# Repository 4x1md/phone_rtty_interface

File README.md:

# RTTY/AFSK Interface for Android Phone or Tablet

## Overview

This interface board was designed for experimenting with RTTY, SSTV and other digital modes with my Yaesu FT-817ND transceiver using [DroidRTTY](https://play.google.com/store/apps/details?id=com.wolphi.droidrtty&hl=en) and [DroidSSTV](https://play.google.com/store/apps/details?id=com.wolphi.sstv&hl=en) applications on an Android phone.

## Reference circuits

The idea of this circuit is not new. Many of its variants were published in the internet and the difference between them is relatively small. Usually different versions use different transistors and diodes and some resistors and capacitors values vary but the circuit remains the same.

One of my sources was the article [An AFSK Interface for Android Smartphones](https://github.com/4x1md/phone_rtty_interface/blob/master/docs/An_AFSK_Interface_for_Android_Smartphones.pdf) by Wolfgang Philips, W8DA, and Martin Huyett, K0BXB, which was published in the May 2012 issue of QST.

More circuits are available in [links section](#links) of this document.

## Revision A

The interface has two revisions. The difference between the two is relatively small. Circuit description and mechanics presented further down in this document are relevant for both revisions.

For the schematics and the photos of the first revision please refer to [revision_a.md](https://github.com/4x1md/phone_rtty_interface/blob/master/docs/revision_a.md)

If you got a blue PCB from me, you have the first revision board.

## Schematic

J1 connects the interface to a phone or tablet. It is a generic 4-pole 3.5mm jack. Its pinout is the same as that of Android phones. Using this jack makes connecting the phone or tablet easy requiring only a simple 3.5mm-to-3.5mm TRRS jack cable. No custom cables are required.

R1 and R2 prevent short-circuit of phone outputs. Their values are not critical and can be in the range of 10 to 51 Ohm. R1 connects the output of the right channel and R2 connects the left. One channel or both can be used. If only one channel is used, only the corresponding resistor should be assembled. In this configuration a wire jumper can be used instead of a resistor.

Transistor Q1 is a common emitter voltage amplifier stage. It is powered from the phone by the DC voltage which usually powers external microphone.

The bias resistors of this stage are R3, R4 and R5. These three resistors allow building two different amplifier types. All the three should not be assembled at the same time. Assembling R5 only creates a shunt feedback stage. In this case R3 and R4 are not required. If R3 and R4 are assembled the amplifier becomes voltage divider biased stage without AC feedback. In this case R5 is not required. These three resistor footprints leave some field for experimenting which is an essential part of the amateur radio.

Diodes D1 and D2 rectify the amplified signal and create DC bias for Q2 which pulls down the PTT line of the transceiver. Different versions of this circuit use different types of diodes. Some use silicon diodes, others use Shottkys. My assembled version worked well with 1N4148 silicon diodes. Replacing them with BAT46 Shottkys increased the rectifier output voltage. Germanium diodes like 1N34 or 1N60 should work as well in this circuit.

Transistor Q2 pulls the PTT line of the transceiver down. The PTT line of FT-817ND has pull-up resistors network with total resistance of 11 kOhm. It means that the current needed to pull the PTT voltage down to zero is 0.45 mA. It requires bias current of Q2 to be about 20 microamperes. In actual circuit the voltage on C6 will be about 0.8V which will be enough to bias Q2 into saturation.

Resistor R15 discharges C6 when the PTT line needs to be released. It is required if Q2 is a MOSFET. It was added in the second version of the interface.

The design features two connectors for connecting a transceiver. P1 is a 6-pin mini-DIN connector which is pin-compatible with DATA connector of Yaesu FT-817. The second connector, J2 is 4-pole 3.5mm jack. It is a generic connector which can also be used to connect transceivers. The 3.5mm TRRS jack does not have PTT line. Two connectors are put for redundancy. In actual circuit only one or both can be assembled depending on requirements.

Both connectors have 1200 bps and 9600 bps lines and switch SW1 is used to choose between the two data rates. If only one data rate is required, the corresponding switch pins can be shorted with a wire jumper without assembling the switch itself.

C7 and C8 are RF-blocking capacitors thus ceramic ones are preferred. Other components are not critical. Most of them can be pulled of old electronic equipment.

## Circuit analysis

If you like exploring oscilloscope output, doing some math and want more details about this circuit, please refer to [circuit_description.md](https://github.com/4x1md/phone_rtty_interface/blob/master/docs/circuit_description.md).

If you like simulating circuits, refer to [circuit_simulations.md](https://github.com/4x1md/phone_rtty_interface/blob/master/docs/circuit_simulations.md) for LTspice simulations.

## BOM variants

The second revision of the interface Q2 can be BJT or MOSFET.

### BJT version

### MOSFET version

The rectifier output voltage reaches approximately 2.2V when loaded with a high resistance. Therefore, a low threshold N-channel MOSFET is recommended for this circuit. For example, VN2410L has maximum Vth of 2.0V, which makes it a good choice. However, a general purpose MOSFET with a higher Vth might work too. In my circuit I used 2N7000 which has maximum threshold of 3.0V and it works well.

If Q2 is a MOSFET, R15 is require for discharging C6. Without R15, C6 will remain charged after the first transmit and the PTT line will never be released.

## Connectors pinout

The following diagram shows the pinout of the external connectors. The phone is connected using 3.5mm jack J1. The transceiver can be connected to the 6-pin Mini-DIN connector P1 or to the 3.5mm jack J2. Connectors P1 and J2 are electrically connected. The PTT line is connected to P1 only.

## Design

### Requirements and considerations

 - Enclosure box.
 - Small size.
 - Easy-to-get parts.
 - Adjusting potentiometers from front or rear panel.
 - No proprietary connectors.
 - Easy assembly.
 - Good repeatability by other hams.
 - Options for experiments.

### Mechanics

When I started the development, I decided to assemble the device in an enclosure box. The box had to be inexpensive and easily available from different electronic parts suppliers.

After some search I found a blue aluminium box 58x50x24mm. The box is relatively cheap and can be purchased from many sellers on eBay or AliExpress. The box fits a PCB of 50x50mm which is enough for this project and has front and rear panels which can be modified by drilling or cutting. In order to eliminate the drilling process, in revision B I created front and rear panels from PCBs.

### PCB development

The PCB was designed using KiCAD software as a simple two-layer board with through-hole mounted parts.

<!--  -->

<!--  -->

### Front and rear panels

Both front and rear panels were made from PCBs. Their fuction is mechanical only and no electronic parts are assembled on these PCBs.

## Photo gallery

### Factory-produced PCB

The PCBs were produced by PCBWay who did a great job. Solder mask of the first revision was made blue in order to match the color of the enclosure box. The second revision was produced with green solder mask.

<!--  -->

:warning: **Important Note!**
Minimum order at the factory was 10 boards from which I need only two or three. As of April 15, 2020, I have board sets (main PCB, front and rear panel), which I can give away. If you'd like to build this device for yourself, I can send you a board. Feel free to contact me.

### Populated PCB

The design uses through hole parts which make PCB assembly quite simple. Connectors, trimmer potentiometers and switch are new. All the other components were recovered from old electronic equipment.

### Assembled device

I haven't yet completed drilling the front and the rear panel of the box, so the device isn't yet fully assembled. The following photos show that the PCB perfectly fits in the chosen box.

The complete device with front and rear panel assembled:

### Field tests and using the device

Cuba to Israel. Nice DX!

## Known issues

The developers of [Wolphi-Link interface](http://www.wolphi.com/interface/) report the following issue:

```WolphiLink might not work properly if you transmit on VHF or UHF while having your antenna to close to your phone/tablet and WolphiLink. The PTT might get triggered by RF and would not release.```

I experienced the same behavior on VHF and UHF bands especially when trying to transmit in AM, FM or PKT modes. When the transmitting antenna is close to the board the transceiver remains in TX mode and the only way to release it is to turn it off. The issue usually disappears when the phone is disconnected even if its cable is still connected to the jack.

I suppose that the cables between the transceiver and the phone become a counterpoise of the transmitting antenna and the generated RF causes transceiver keying. I don't know if this issue exists with other transceivers.

Till now, I couldn't find any solution. On HF bands and when the transmitting antenna is far from the transceiver the device functions properly.

**Update:** After connecting a shielded cable between the transceiver and the interface, the problem is almost completely.

## Adjustments

A properly assembled device should require only RX and TX level adjustments using R10 and R11 trimmer potentiometers.

## Plans for future development

If I ever do another revision of this board, I'd like to make the following improvements:

1. [x] Adding an RF-blocking capacitor to the PTT line.
2. [x] Adding PTT line to J2 3.5mm jack.
3. [x] Adding a capacitor in parallel to R5 for limiting the bandwidth of the amplifier.
4. [x] Removing ground conductor from the component layer.
5. [x] Improving the thermal relief on the grounded pads. Today they are sometimes hard to solder.
6. [x] Increasing the space between R10 and R11 to fit larger trimmer resistors.
7. [ ] Adding a TX inhibit switch which will disable triggering the PTT line. It may be useful to prevent notifications or other non radio-related sounds to key the transceiver.

## Links
* Designing a Phone/Radio interface: [Part 1](https://waynemerry.wordpress.com/2012/08/16/designing-a-phoneradio-interface/), [Part 2](https://waynemerry.wordpress.com/2012/08/22/ft-817-phone-audio-interface-part-2/), [Part 3](https://waynemerry.wordpress.com/2012/11/02/ft-817-ft-897-phone-audio-interface-part-3/)
* http://www.darc-husum.de/android-interface.html
* https://www.dk9jc.de/blog/equipment/109-ft-817-smartphone-interface-for-pskdroid-and-aprsdroid
* [DroidSSTV manual](http://www.wolphi.com/ham-radio-apps/droidsstv-2/droidsstv-manual/)
* [Wolphi-Link interface](http://www.wolphi.com/interface/)
* http://161wt001.blogspot.com/2013/11/construction-interface-sstv-psk-rtty.html
* https://oe6fte.com/wolphilink-android-interface/
* https://g4fre.blogspot.com/2014/02/rtty-and-psk31-transceive-with-nexus-7.html
* http://wa8lmf.net/ham/tonekeyer.htm
* https://9m2pju.blogspot.com/2012/05/droidpsk-psk-on-your-android-phone.html
* Enclosure box: http://www.ebay.com/itm/171186884639

## Questions? Suggestions?
You are more than welcome to contact me with any questions, suggestions or propositions regarding this project. You can:

1. Visit [my QRZ.COM page](https://www.qrz.com/db/4X5DM)
2. Visit [my Facebook profile](https://www.facebook.com/Dima.Meln)
3. Write me an email to iosaaris =at= gmail dot com

## How to Support or Say Thanks

If you like this project, or found here some useful information and want to say thanks, or encourage me to do more, you can buy me a coffee!

You can aslo make a donation with PayPal:

---

**73 de 4X1MD**

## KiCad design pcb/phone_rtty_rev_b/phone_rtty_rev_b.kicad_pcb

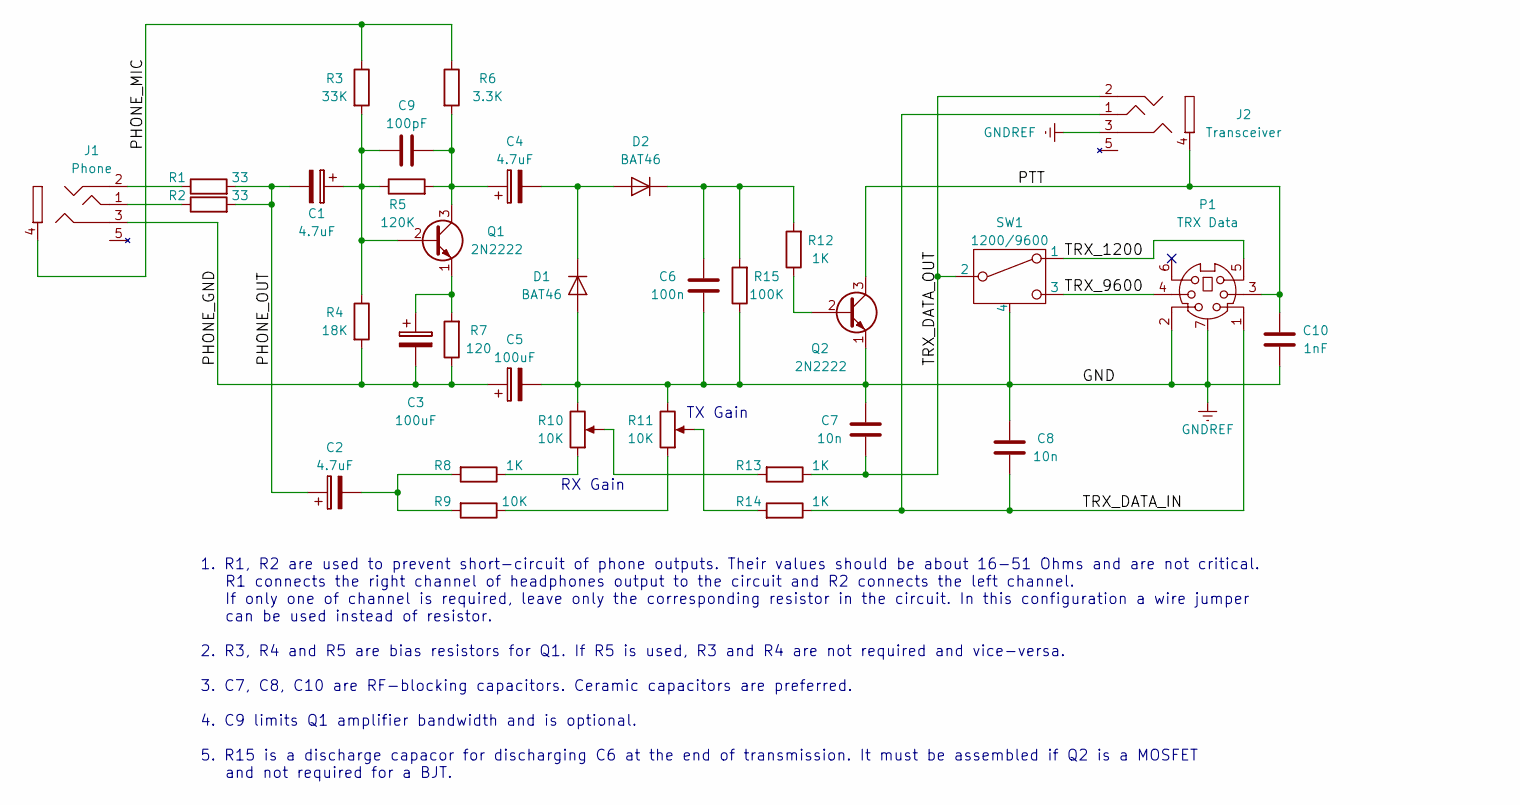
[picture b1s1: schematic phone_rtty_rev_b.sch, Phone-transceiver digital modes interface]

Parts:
C1, C2, C4: 4.7uF; CP_Radial_D5.0mm_P2.50mm
C3, C5: 100uF; CP_Radial_D5.0mm_P2.50mm
C6: 100n; C_Rect_L7.0mm_W2.0mm_P5.00mm
C7, C8: 10n; C_Disc_D4.3mm_W1.9mm_P5.00mm
C9: 100pF; C_Disc_D4.3mm_W1.9mm_P5.00mm
C10: 1nF; C_Disc_D4.3mm_W1.9mm_P5.00mm
D1, D2: BAT46; D_DO-35_SOD27_P7.62mm_Horizontal
J1: Phone; PJ320E_3.5mm_Jack
J2: Transceiver; PJ320E_3.5mm_Jack
P1: TRX Data; Connector_Mini-DIN_Female_6Pin_2rows
Q1, Q2: 2N2222; TO-92_Molded_Wide_Oval
R1, R2: 33; R_Axial_DIN0204_L3.6mm_D1.6mm_P2.54mm_Vertical
R3: 33K; R_Axial_DIN0207_L6.3mm_D2.5mm_P10.16mm_Horizontal
R4: 18K; R_Axial_DIN0207_L6.3mm_D2.5mm_P10.16mm_Horizontal
R5: 120K; R_Axial_DIN0207_L6.3mm_D2.5mm_P10.16mm_Horizontal
R6: 3.3K; R_Axial_DIN0207_L6.3mm_D2.5mm_P10.16mm_Horizontal
R7: 120; R_Axial_DIN0207_L6.3mm_D2.5mm_P2.54mm_Vertical
R8, R12, R13, R14: 1K; R_Axial_DIN0207_L6.3mm_D2.5mm_P10.16mm_Horizontal
R9: 10K; R_Axial_DIN0207_L6.3mm_D2.5mm_P10.16mm_Horizontal
R10, R11: 10K; Potentiometer_Trimmer_Vertical_Multi_Compatible
R15: 100K; R_Axial_DIN0207_L6.3mm_D2.5mm_P10.16mm_Horizontal
SW1: 1200/9600; Cliff_UT1x_SPDT_ON-ON_Switch_Short

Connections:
/PHONE_GND: C3.2, C5.1, J1.3 (GND), R4.2, R7.1
/PHONE_MIC: J1.4 (Mic), R3.1, R6.1
/PHONE_OUT: C1.2, C2.1, R1.2, R2.2
/PTT: C10.1, J2.4 (Mic), P1.3, Q2.3 (C)
/TRX_1200: P1.5, SW1.1
/TRX_9600: P1.4, SW1.3
/TRX_DATA_IN: C8.1, J2.1 (R), P1.1, R14.1
/TRX_DATA_OUT: C7.1, J2.2 (L), R13.1, SW1.2
GNDREF: C5.2, C6.2, C7.2, C8.2, C10.2, D1.2 (A), J2.3 (GND), P1.2, P1.7 (Shell), Q2.1 (E), R10.3, R11.3, R15.1, SW1.4
unnamed: C1.1, C9.2, Q1.2 (B), R3.2, R4.1, R5.1
unnamed: C2.2, R8.2, R9.2
unnamed: C3.1, Q1.1 (E), R7.2
unnamed: C4.1, C9.1, Q1.3 (C), R5.2, R6.2
unnamed: C4.2, D1.1 (K), D2.2 (A)
unnamed: C6.1, D2.1 (K), R12.2, R15.2
unnamed: J1.1 (R), R2.1
unnamed: J1.2 (L), R1.1
unnamed: Q2.2 (B), R12.1
unnamed: R8.1, R10.1
unnamed: R10.2, R13.2
unnamed: R9.1, R11.1
unnamed: R11.2, R14.2

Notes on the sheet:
RX Gain
TX Gain
1. R1, R2 are used to prevent short-circuit of phone outputs. Their values should be about 16-51 Ohms and are not critical. R1 connects the right channel of headphones output to the circuit and R2 connects the left channel. If only one of channel is required, leave only the corresponding resistor i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

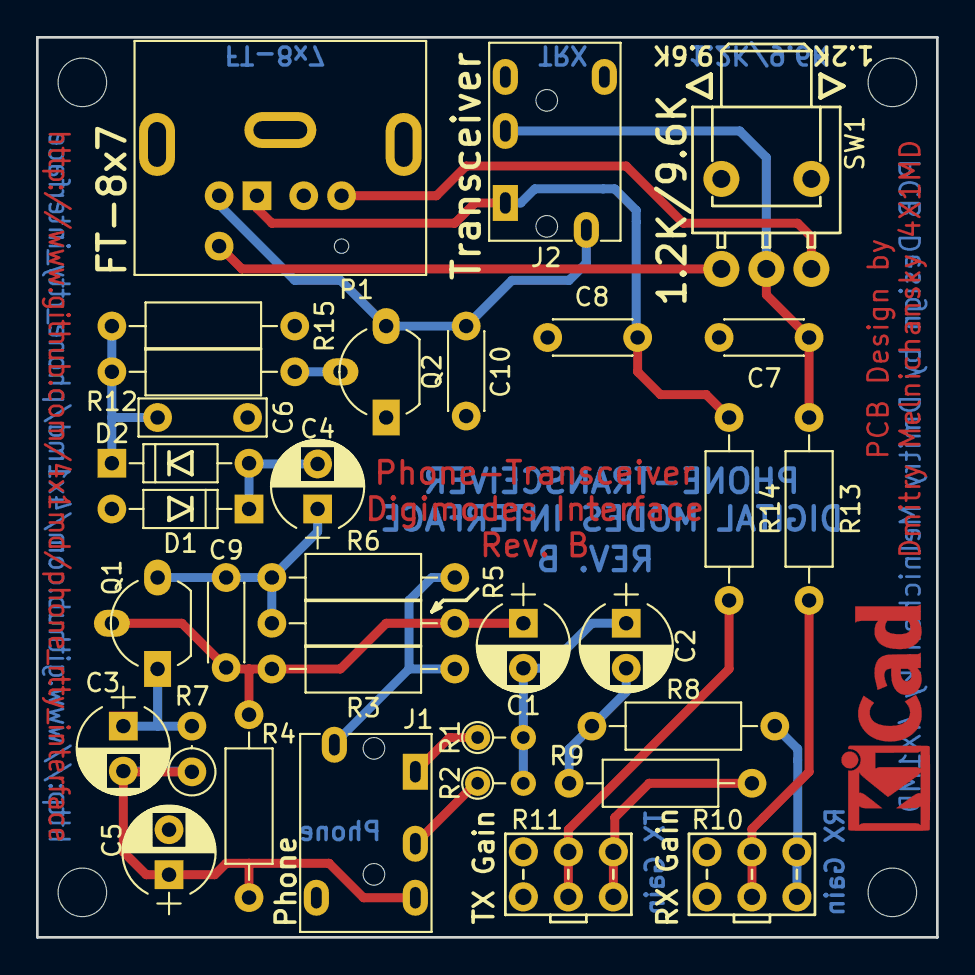
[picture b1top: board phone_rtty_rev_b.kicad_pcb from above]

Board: 2 copper layers, 50.0 x 50.0 mm, 37 parts (0 on the bottom side), 22 nets.

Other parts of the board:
MH1, MH2, MH3, MH4: MH_2.7mm_M2.5_ISO7380; MountingHole_2.7mm_M2.5_ISO7380

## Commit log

2017-04-11 Images.
2017-04-11 README.md
2017-04-11 KiCad project and Gerbers.
2017-04-11 Article from QST.
2017-04-12 Revision info.
2017-10-05 QSL image.
2017-10-12 Image.
2017-10-12 Readme.
2017-10-12 circuit_description.md
2017-10-12 Removed png image.
2017-10-12 Circuit description and oscilograms.
2017-10-12 Circuit description.
2017-10-12 Deleted image.
2017-10-12 Project description.
2017-10-21 PCB revision A.
2017-10-28 PCB rev. B first commit.
2017-10-28 Potentiometers holes on the front panel.
2017-10-31 Minor changes.
2017-12-02 Deleted unnecessary files.
2017-12-02 Minor changes to revision B and gerbers.
2017-12-16 Main board and panels corrections.
2017-12-20 Updated gerbers to last version.
2018-01-15 Minor change.
2018-01-16 Updated circuit description.
2018-03-24 LTspice simulations, readme file and images.
2018-04-05 LTspice simulations.
2018-04-06 Simulations.
2018-04-06 Simulations description.
2018-10-01 Updated resistor value on the schematic.
2018-10-01 gitignore
2020-04-15 Footprints data.
2020-04-15 Revision A description.
2020-04-15 Added revision B description.
2020-04-15 Update.
2021-06-07 External connections.
